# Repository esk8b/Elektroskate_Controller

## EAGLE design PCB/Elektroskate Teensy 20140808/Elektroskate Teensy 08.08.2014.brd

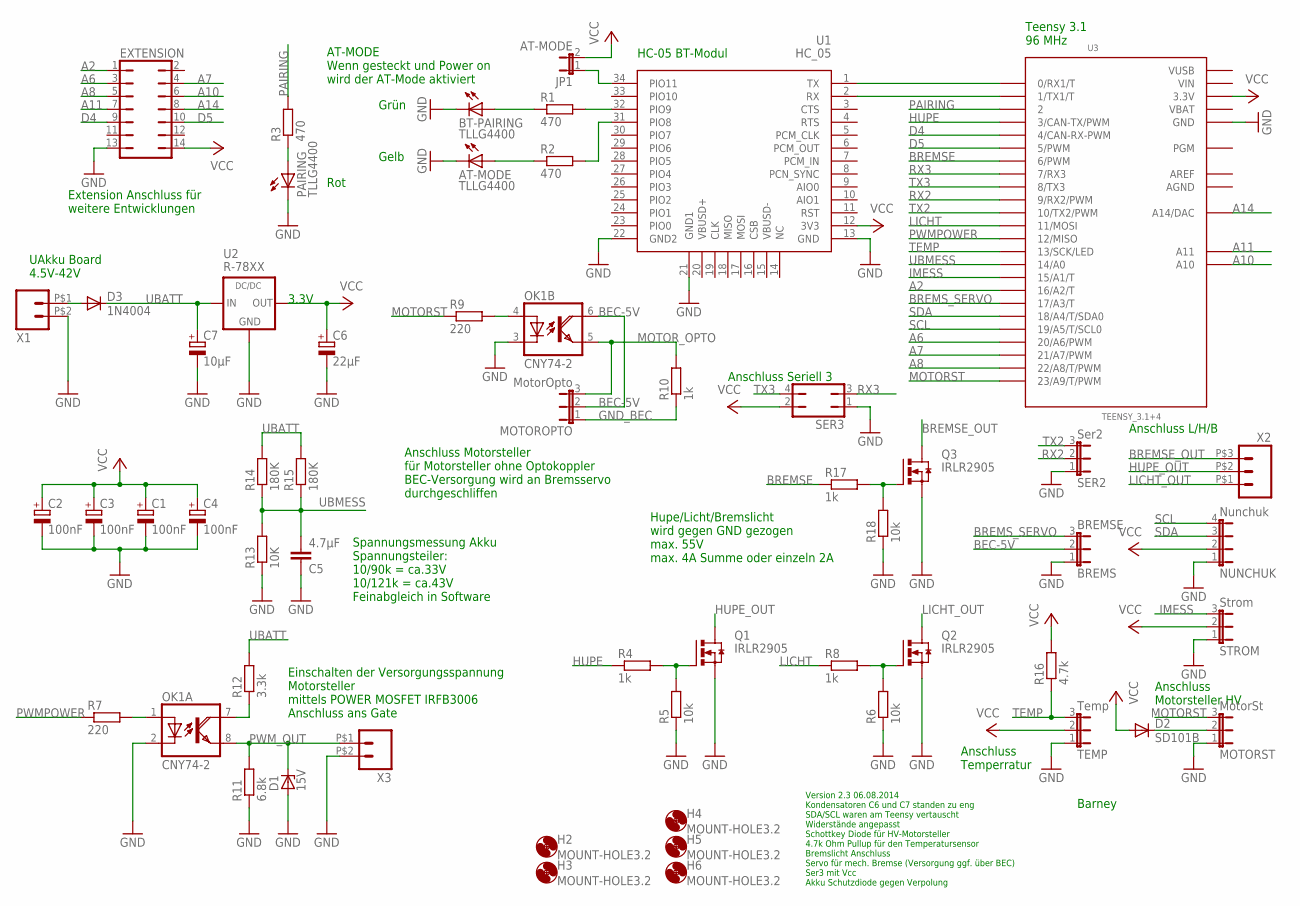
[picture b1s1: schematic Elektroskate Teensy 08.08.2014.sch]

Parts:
AT-MODE: TLLG4400; LED3MM
BREMS: BREMSE; JP2
BT-PAIRING: TLLG4400; LED3MM
C1, C2, C3, C4: 100nF; B45181A
C5: 4.7µF; C025-024X044
C6: 22µF; E2,5-5
C7: 10µF; E2-4
D1: 15V; DO35Z10
D2: SD101B; SOD123
D3: 1N4004; DO41-10
EXTENSION: JP7Q
H2, H3, H4, H5, H6: MOUNT-HOLE3.2; 3,2
JP1: AT-MODE; JP1
MOTOROPTO: MotorOpto; JP2
MOTORST: MotorSt; JP2
NUNCHUK: Nunchuk; JP4
OK1: CNY74-2; DIL08
PAIRING: TLLG4400; LED3MM
Q1, Q2, Q3: IRLR2905; D-PAK_TO252AA
R1, R2, R3: 470; 0207/10
R4, R8, R10, R17: 1k; 0207/10
R5, R6, R18: 10k; 0207/10
R7, R9: 220; 0207/10
R11: 6.8k; 0207/10
R12: 3.3k; 0207/10
R13: 10K; 0207/10
R14, R15: 180K; 0207/10
R16: 4.7k; R0805
SER2: Ser2; JP2
SER3: JP2Q
STROM: Strom; JP2
TEMP: Temp; JP2
U1: HC_05; BLUETOOTH_SMD
U2: R-78XX
U3: TEENSY_3.1+4
X1, X3: PSS254_2GEWINKELT; 02W
X2: PSS254_3GEWINKELT; 03W

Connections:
A2: EXTENSION.1, U3.16/A2 (16/A2/T)
A6: EXTENSION.3, U3.20/A6 (20/A6/PWM)
A7: EXTENSION.4, U3.21/A7 (21/A7/PWM)
A8: EXTENSION.5, U3.22/A8 (22/A8/T/PWM)
A10: EXTENSION.6, U3.A10
A11: EXTENSION.7, U3.A11
A14: EXTENSION.8, U3.A14 (A14/DAC)
AGND: U3.AGND
AREF: U3.AREF
BEC-5V: BREMS.2, MOTOROPTO.2, OK1.6 (COL)
BREMSE: R17.1, U3.6 (6/PWM)
BREMSE_OUT: Q3.4 (D), X2.P$3 (3)
BREMS_SERVO: BREMS.3, U3.17/A3 (17/A3/T)
D4: EXTENSION.9, U3.4 (4/CAN-RX-PWM)
D5: EXTENSION.10, U3.5 (5/PWM)
GND: AT-MODE.K (C), BREMS.1, BT-PAIRING.K (C), C1.-, C2.-, C3.-, C4.-, C5.1, C6.-, C7.-, D1.A, EXTENSION.13, MOTORST.1, NUNCHUK.1, OK1.2 (C), OK1.3 (C), PAIRING.K (C), Q1.3 (S), Q2.3 (S), Q3.3 (S), R5.1, R6.1, R11.1, R13.1, R18.1, SER2.1, SER3.1, STROM.1, TEMP.1, U1.13 (GND), U1.21 (GND1), U1.22 (GND2), U2.2 (GND), U3.GND, U3.GND1 (GND), X1.P$2 (2), X3.P$2 (2)
GND_BEC: MOTOROPTO.1, R10.1
HUPE: R4.1, U3.3 (3/CAN-TX/PWM)
HUPE_OUT: Q1.4 (D), X2.P$2 (2)
IMESS: STROM.3, U3.15/A1 (15/A1/T)
LICHT: R8.1, U3.11 (11/MOSI)
LICHT_OUT: Q2.4 (D), X2.P$1 (1)
MOTORST: MOTORST.3, R9.1, U3.23/A9 (23/A9/T/PWM)
MOTOR_OPTO: MOTOROPTO.3, OK1.5 (EMI), R10.2
unnamed: U1.1 (TX), U3.0 (0/RX1/T)
unnamed: U1.2 (RX), U3.1 (1/TX1/T)
unnamed: BT-PAIRING.A, R1.1
unnamed: PAIRING.A, R3.1
unnamed: OK1.4 (A), R9.2
unnamed: R2.2, U1.31 (PIO8)
unnamed: AT-MODE.A, R2.1
unnamed: R1.2, U1.32 (PIO9)
unnamed: OK1.7 (COL), R12.1
unnamed: OK1.1 (A), R7.2
unnamed: D2.C, MOTORST.2
unnamed: Q3.1 (G), R17.2, R18.2
unnamed: D3.A, X1.P$1 (1)
unnamed: Q1.1 (G), R4.2, R5.2
unnamed: Q2.1 (G), R6.2, R8.2
unnamed: JP1.1, U1.34 (PIO11)
PAIRING: R3.2, U3.2
PWMPOWER: R7.1, U3.12 (12/MISO)
PWM_OUT: D1.C, OK1.8 (EMI), R11.2, X3.P$1 (1)
RX2: SER2.2, U3.9 (9/RX2/PWM)
RX3: SER3.3, U3.7 (7/RX3)
SCL: NUNCHUK.4, U3.19/A5 (19/A5/T/SCL0)
SDA: NUNCHUK.3, U3.18/A4 (18/A4/T/SDA0)
TEMP: R16.1, TEMP.3, U3.13 (13/SCK/LED)
TX2: SER2.3, U3.10 (10/TX2/PWM)
TX3: SER3.4, U3.8 (8/TX3)
UBATT: C7.+, D3.C, R12.2, R14.2, R15.2, U2.1 (IN)
UBMESS: C5.2, R13.2, R14.1, R15.1, U3.14/A0
VBAT: U3.VBAT
VCC: C1.+, C2.+, C3.+, C4.+, C6.+, D2.A, EXTENSION.14, JP1.2, NUNCHUK.2, R16.2, SER3.2, STROM.2, TEMP.2, U1.12 (3V3), U2.3 (OUT), U3.3.3V, U3.3.3V1 (3.3V)
VIN: U3.VIN
VUSB: U3.VUSB

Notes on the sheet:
Barney
Version 2.3 06.08.2014 Kondensatoren C6 und C7 standen zu eng SDA/SCL waren am Teensy vertauscht Widerstände angepasst Schottkey Diode für HV-Motorsteller 4.7k Ohm Pullup für den Temperatursensor Bremslicht Anschluss Servo für mech. Bremse (Versorgung ggf. über BEC) Ser3 mit Vcc Akku Schutzdiode ge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
UAkku Board 4.5V-42V
Spannungsmessung Akku Spannungsteiler: 10/90k = ca.33V 10/121k = ca.43V Feinabgleich in Software
Einschalten der Versorgungsspannung Motorsteller mittels POWER MOSFET IRFB3006 Anschluss ans Gate
Anschluss Motorsteller für Motorsteller ohne Optokoppler BEC-Versorgung wird an Bremsservo durchgeschliffen
Hupe/Licht/Bremslicht wird gegen GND gezogen max. 55V max. 4A Summe oder einzeln 2A
AT-MODE Wenn gesteckt und Power on wird der AT-Mode aktiviert
HC-05 BT-Modul
Teensy 3.1 96 MHz
Extension Anschluss für weitere Entwicklungen
Rot
Gelb
Grün
Anschluss L/H/B
Anschluss Motorsteller HV
Anschluss Temperratur
Anschluss Seriell 3

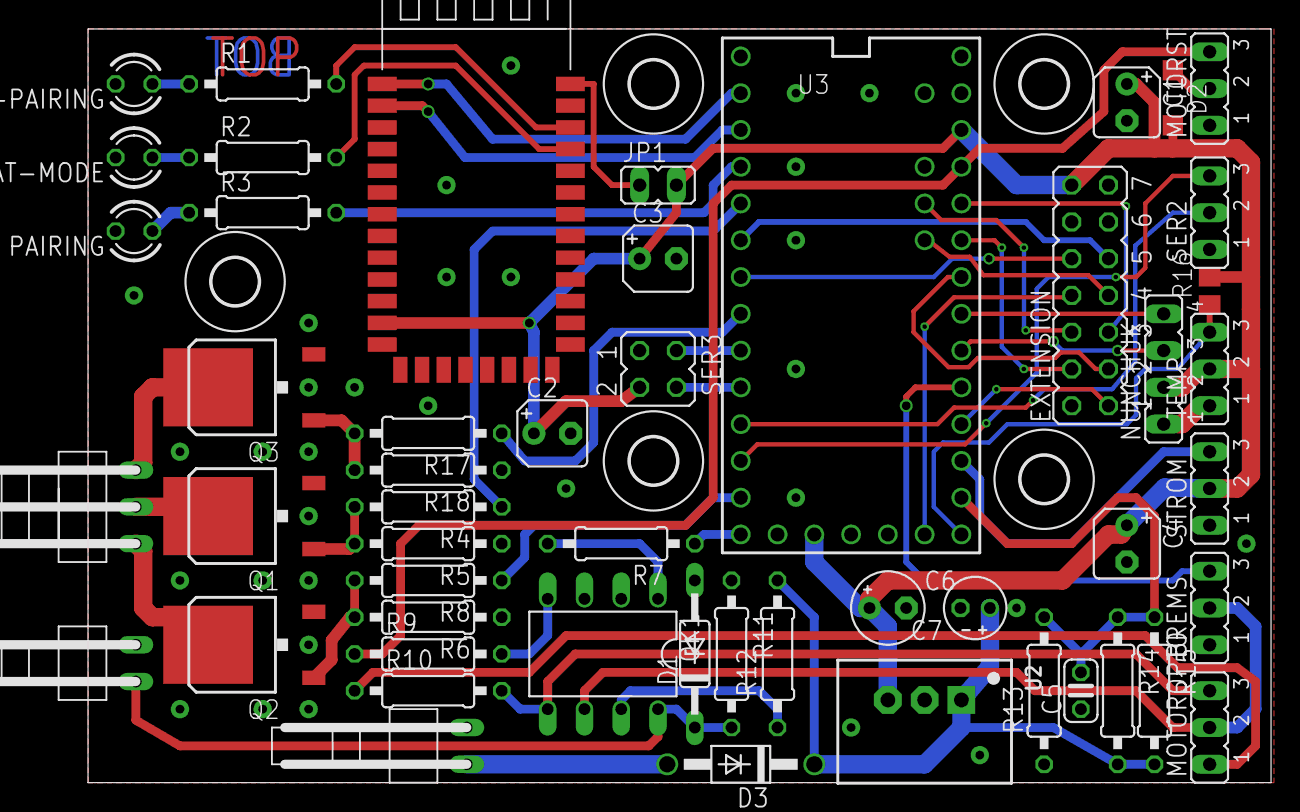
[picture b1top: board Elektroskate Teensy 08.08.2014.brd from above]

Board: 2 copper layers, 85.8 x 52.1 mm, 56 parts (0 on the bottom side), 51 nets.

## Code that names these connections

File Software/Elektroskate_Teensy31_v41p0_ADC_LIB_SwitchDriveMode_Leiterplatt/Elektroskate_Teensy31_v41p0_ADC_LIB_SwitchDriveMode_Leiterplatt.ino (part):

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uint8_t  PairingStatus = LOW;          // Beim Einschalten besteht kein Pairing
uint16_t PairingLostCounter = 0;       // wird hoch gezaehlt, wenn accelX hintereinander gleiche Werte liefert
uint16_t PairingSuccessCounter = 0;    // wird hoch gezaehlt, wenn accelX hintereinander ungleiche Werte liefert
uint16_t accelXAlt = 0;                // Alter Beschleunigungswert X fuers Pairing und Funkabrisserkennung

// PWM Motorsteuerung
#define PWMFrequenz 50                 // PWM Frequenz fuer die Ansteuerung des Motorstellers: alle 20ms einen Impuls in der Laenge von 1.0 bis 2.0ms
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uint16_t TempSensor;

// Ubatt, Strom und Leistungsmessung
float Ubatt = 0;                      // Spannung Batterie in V gemessen
float Strom[10] = {0};                // Strommessung Array, der Strom kann auch negativ werden, es wird ein Array zum Mitteln verwendet
uint16_t StromIndex = 0;              // Zeiger fuer den Strom
float Momentanleistung = 0;           // Aktuelle Leistung, die gerade aufgenommen wird
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#define StromFaktor (float) 2*StromMMax/AnalogReadResolutionValue  // Umrechnungsfaktor Strom

// Strombegrenzung und Kurzschlusserkennung
#define Reduktionsgewichtung (float) (100/(Ishort-Imax)) // Der Reduktionsfaktor Bf = 100-((Imess-Imax)*Reduktionsgewichtung) in %
float Reduktionsfaktor = 0;           // Reduktionsfaktor(%): Stellwert = (Stellwertmomentan-Motorneutralstellung)*Reduktionsfaktor + Motorneutralstellung
float Imomentan = 0;                  // Momentanstrom, wird abgeleitet von Strom[0] oder Ishort
uint8_t F_Ueberstrom = LOW;           // Sollte ein Uebserstrom erkannt werden, wird eine Reduzierung des Motorstellwertes durchgefuehrt
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void setup()
{
  // ADC Einstellungen
  pinMode(Pin_Ubatt, INPUT);                            // Spannungsmesspin aktivieren
  pinMode(Pin_Strom, INPUT);                            // Strommesspin aktivieren
  // ADC_0
  adc->setReference(ADC_REF_EXT, ADC_0);           // Bei Extern wird die ca. 3.3V Versorgungsspannung des Teensys benutzt
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  adc->setSamplingSpeed(ADC_VERY_LOW_SPEED, ADC_1);     // change the sampling speed
  // Continuous Abfragemodus kann erst ab Platine v2.5 verwendet werden (Verwendung der Pins A0, A2 statt A0, A1)
  // Abfragezeit der ADC sinkt unter 4us.
  adc->startContinuous(Pin_Ubatt, ADC_0);               // Starte die Dauermessung der beiden ADC im Hintergrund
  adc->startContinuous(Pin_Strom, ADC_1);               // Dies beschleunigt die Messwerterfassung um das 150-fache
                                                        // (damit wird auch die Verwendung einer hohen Meßwertanzahl zum Averaging möglich)
  adc->analogReadContinuous(ADC_0);                     // Messwertabfrage des ADC_0 ab (Achtung asynchron)
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  // DAC Einstellungen
  analogWriteFrequency(Pin_Motorstelleranschluss_A, PWMFrequenz); // Einstellen der PWM Parameter fuer den Motorsteller
  analogWriteFrequency(Pin_Motorstelleranschluss_B, PWMFrequenz); // Einstellen der PWM Parameter fuer den Motorsteller
  analogWriteFrequency(Pin_Brems_Servo, PWMFrequenz);             // Einstellen der PWM Parameter fuer den Motorsteller
  analogWriteResolution(AnalogWriteResolutionBits);               // Analog Aufloesung auf 16 Bit einstellen

  // Zyklischer IRQ-Timer die einen Software Interrupt ausloest
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  Serial1.begin(BT_BAUDRATE);    // Werteausgabe ueber Serieller mittels Bluetooth definieren

  // Alle Ausgangspins definieren
  pinMode(Pin_Hupe, OUTPUT);          // Hupe ist ein Ausgang
  pinMode(Pin_Licht, OUTPUT);         // Licht ist ein Ausgang
  pinMode(Pin_Bremse, OUTPUT);        // Bremslicht ist ein Ausgang
  pinMode(Pin_Blinker_L, OUTPUT);     // Blinker Links ist ein Ausgang
  pinMode(Pin_Blinker_R, OUTPUT);     // Blinker Rechts ist ein Ausgang
  pinMode(Pin_ReceiverLED, OUTPUT);   // ReceiverLED ist ein Ausgang
  pinMode(Pin_PowerSwitch, OUTPUT);   // Power MOSFET ist ein Ausgang

  // Startwert der Ausgaenge definieren
  digitalWrite(Pin_Hupe, LOW);        // Hupe aus
  digitalWrite(Pin_Licht, LOW);       // Licht aus
  digitalWrite(Pin_Bremse, LOW);      // Bremslicht aus
  digitalWrite(Pin_Blinker_L, LOW);   // Blinker Links aus
  digitalWrite(Pin_Blinker_R, LOW);   // Blinker Rechts aus
  digitalWrite(Pin_ReceiverLED, LOW); // Empfangsstatus LED aus
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    StellWertMotor = LeerlaufStellWertMotor;                            // StellWertMotor auf Leerlauf setzen
    analogWrite(Pin_Motorstelleranschluss_A, LeerlaufStellWertMotor);   // PWM Register Motorstellwert-A auf Leerlauf
    analogWrite(Pin_Motorstelleranschluss_B, LeerlaufStellWertMotor);   // PWM Register Motorstellwert-B auf Leerlauf
    analogWrite(Pin_Brems_Servo, PWM_Bremse_Ungebremst * AnalogWriteResolutionValue * PWMFrequenz / 1000); // PWM Register Bremsservo auf Bremse loesen
    PairingSuccessCounter = 0;                                          // ParingSuccessCounter zuruecksetzen
    while (PairingStatus == LOW) {                                      // Solange pruefen, bis die Verbindung steht
      accelXAlt = accelX;                                               // Alten Wert des Beschleunigungssensors ablegen
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void Funkabriss() {
  // Totmannschalter und Funkabriss pruefen
  if (DEBUG_Funktion) Serial_B.println("Funktion: Funkabriss");
  digitalWrite(Pin_ReceiverLED, HIGH);              // Pairing steht, Status ReceiverLED an
  accelXAlt = accelX;
  Nunchuk_auslesen();
  if (accelX == accelXAlt || accelXAlt > 1024) {    // Wahrscheinlichkeitspruefung Funkabriss
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  // Bremsservostellwert und Bremslicht setzen

  if (StellWertMotor <  LeerlaufStellWertMotor) {
    digitalWrite(Pin_Bremse, HIGH);                    // Bremslicht an
    analogWrite(Pin_Brems_Servo, StellWertBremse_max); // PWM Register Bremsservo auf Vollbremse
    if (DEBUG_Bremse) {
      Serial_B.print("PWM_Bremse_Vollbremse: ");
      Serial_B.println(StellWertBremse_max);
    }
  }
  else {
    digitalWrite(Pin_Bremse, LOW);                     // Bremslicht aus
    analogWrite(Pin_Brems_Servo, StellWertBremse_off); // PWM Register Bremsservo auf Bremse loesen
    if (DEBUG_Bremse) {
      Serial_B.print("PWM_Bremse_Ungebremst: ");
      Serial_B.println(StellWertBremse_off);
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  if (DEBUG_Funktion) Serial_B.println("Funktion: Licht_Hupe");
  if (cButton == LOW) cButtonZero = LOW;                           // Trigger auf ansteigende Flanke, damit Licht nicht blinkt
  if (cButton == HIGH && cButtonZero == LOW && analogX_12bit < XAchseLinks_12bit) {  // Toggle Licht Nunchuck X < 30
    digitalWrite(Pin_Licht, !digitalRead(Pin_Licht));
    cButtonZero = HIGH;                                            // Licht gegen Blinken sperren
  }
  if (cButton == HIGH && analogX_12bit > XAchseLinks_12bit) {      // Hupe an solange C-Taste gedrueckt und X > 30
    digitalWrite(Pin_Hupe, HIGH);
  }
  else {
    digitalWrite(Pin_Hupe, LOW);
  }
}

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    }

    if (LICHTHUPE) {
      digitalWrite(Pin_Hupe, HIGH);                  // Zur Bestaetigung 200ms hupen
      delay (200);
      digitalWrite(Pin_Hupe, LOW);
    }
    zButtonZero = HIGH;                              // Routine gegen Festhalten des Z-Tasters sperren
    if (ObererStellWertMotorUmschaltCounter == 3) {  // Es muss dreimal die Z-Taste und der X-Joystick ausgeloest werden
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      }   
      ObererStellWertMotorUmschaltCounter = 0;       // Counter zuruecksetzen
      if (LICHTHUPE) {
        digitalWrite(Pin_Hupe, HIGH);                // Zur Bestaetigung der Umschaltung 500ms hupen
        delay (500);
        digitalWrite(Pin_Hupe, LOW);
      } 
    }
  }
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    }

    if (LICHTHUPE) {
      digitalWrite(Pin_Hupe, HIGH);      // Zur Bestaetigung 200ms hupen
      delay (200);
      digitalWrite(Pin_Hupe, LOW);
    }
    zButtonZero = HIGH;                  // Routine gegen Festhalten des Z-Tasters sperren
    if (DriveModeUmschaltCounter == 3) { // Es muss dreimal die Z-Taste und der X-Joystick ausgeloest werden
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      DriveModeUmschaltCounter = 0;       // Counter zuruecksetzen
      LeerlaufStellWertMotor = float(PWM_LeerlaufStellWertMotor*AnalogWriteResolutionValue*PWMFrequenz/1000) + (LeerlaufOffset * !DirectDrive); // Update Leerlaufstellwert
      if (LICHTHUPE) {
        digitalWrite(Pin_Hupe, HIGH);     // Zur Bestaetigung der Umschaltung 500ms hupen
        delay (500);
        digitalWrite(Pin_Hupe, LOW);
      }
    }
  }
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
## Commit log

2015-01-11 4.1p0-28.12.2014 Barney: Die Leiterplattenversion v2.5 hat jetzt den Stromsensor an A2. Dadurch kann die ADC-Lib die beiden ADCs getrennt im Teensy parametrieren. Durch die neue Leiterplatte wird der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
2015-01-11 Neue Ordnerstruktur
2015-01-14 Die Strom und Spannungsmessung erfolgt jetzt über die zwei eingebauten ADC-Kanäle ADC_0 und ADC_1. Die Mittelwertbildung wurde von 8 auf 32 angehoben. Eine Messung würde 433µs dauern, es wurde aber d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
2015-01-31 Umstellung auf die Nunchuk Teensy Lib
2015-03-03 Anpassung der Software auf Teensyduino 1.22 und Arduino 1.6.x
2015-03-03 KiCad Projektdateien
2015-03-03 Aktuelle KiCad Datei
2015-03-05 Aktuelle KiCad Daten
2015-03-09 Anpassungen in KiCad PCB Mount Hole hat jetzt die Bohrung 3.2mm Werte der Bauteile nicht mit "," sondern ".". Wichtig für den Export der BOM Bessere Verlegung der Spannungsmessleitung, geschützt in G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
2015-03-21 Anpassung an Arduino IDE 1.61 und Teensyduino 1.21
2015-03-28 Auf BamBam angepasst. HC-05 Rahmen lag auf Pads BrmesOpto Text durch Bremse erstezt Gerber und Drill-Dateien generiert und gesichtet
2015-03-31 Bohrungen für die PC352 und PC353, sowie für die Motorstiftleisten auf 0.965 bzw. 1.0mm vergrößert. Zwei Leiterbahnen wegen Kollisionsmöglichkeit verschoben. Text auf Leiterplatte auf BamBam und Datu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
2015-04-16 Anpassung an die KiCAD Libs >02/2015 Einige kleine Korrekturen am Layout Anpassung der Mounting Holes mit NTPH (nicht durch kontaktieren) Zwei Texte im PCB zugefügt (Tx und Rx Ser2)
2015-04-19 Ab Teensyduino 1.22 wird die Lib ADC und i2c_t3 mitgeliefert und wurde daher aus der library gelöscht. Die Umschaltung DirectDrive und Integraldrive wurde deaktiviert. Die Umschaltung muss gegen vers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
2015-05-01 Files komplett mit aktuellen Dateien aus Barneys zip-Archiv überschrieben.
2015-05-11 Die Version 2.71 hat einige Veränderungen in den Bestückungstext bekommen, Verdeckte Texte wurden Verlagert und noch weitere Informationen an den Anschlüssen ergänzt. Eine Leiterbahn wurde im Quersch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
2015-05-18 Software: Polynom für die Spannungsmessung
2015-05-18 Software: Polynom Spannungsmessung
2015-06-10 4.1p4-28.05.2015 Dude - DEBUG-Flag aus Settings.h entfernt, da ohne Verwendung. Verallgemeinerung der Ausgabe auf 2 generelle Ausgabekanle (USBSerial und BT) - Update Kommentare - Motorsteller-Offset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
2015-06-17 xls mit Augleichspolynom
2015-06-29 Anpassung fuer Arduino 1.6.5.r2 und Teensyduino 1.24 adc.h adc->setReference(ADC_REF_EXT, ADC_0); siehe Dokumentation adc Lib
2015-07-14 Die Libs für den Teensy sind jetzt wieder bei.
2016-12-30 Add files via upload
    Notaus-Anschluss, hält den Motor an, wenn Reißleinenanschluss unterbrochen wird.
2017-09-09 Anpassung Entwicklungsumgebung
    An die aktuelle Arduino 1.8.4 und Teensyduino 1.32 Version
    ADC.h wurde verändert

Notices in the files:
Software/Elektroskate_Teensy31_v41p0_ADC_LIB_SwitchDriveMode_Leiterplatt/Elektroskate_Teensy31_v41p0_ADC_LIB_SwitchDriveMode_Leiterplatt.ino:
Copyright (C) [2012]  [Barney]
This program is free software; you can redistribute it and/or modify it under the terms of
the GNU General Public License as published by the Free Software Foundation; either
Dieses Programm ist freie Software. Sie koennen es unter den Bedingungen der GNU General Public License,
wie von der Free Software Foundation veroeffentlicht, weitergeben und/oder modifizieren,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
